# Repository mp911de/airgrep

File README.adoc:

++++
<h1>
<picture>
<source media="(prefers-color-scheme: dark)" srcset="assets/logo-dark@2x.png">

</picture>
</h1>
++++

A portable ADS-B / FLARM receiver based on https://github.com/PantsForBirds/adsbee[ADSBee].
Started as carrier board for a removable ESP32-S3 touch display and https://pantsforbirds.com/product/adsbee-1090u/[ADSBee 1090U] receiver, with a soldered MAX-M10S GNSS receiver.
It adds a single-cell Li-ion charger, a 5 V boost rail, a fuel gauge, a barometer and a buzzer.

.airgrep Screenshot
image::assets/home-screen.png[airgrep Home Screen,30%]

.Traffic Advisory
image::assets/home-ta.png[airgrep Traffic Advisory,30%]

== Features

* 800x480 Capacitive Touchscreen with ESP32 S3 microcontroller (240 MHz, 16 MB Flash, 8 MB PSRAM)
* https://github.com/PantsForBirds/adsbee[ADSBee 1090U] ADS-B receiver with FLARM firmware and GDL90 Broadcast of FLARM traffic (for e.g. Skydemon, Foreflight, …) via WiFi
* https://www.u-blox.com/en/product/max-m10-series[GPS Module], https://www.bosch-sensortec.com/en/products/environmental-sensors/pressure-sensors/bmp580[Pressure Sensor (for barometric Altitude)]
* link:https://github.com/mp911de/daidalus[DAIDALUS] Traffic Advisory engine (Detect and AvoID)
* Buzzer, WiFi (via ADSBee), USB-C Charging Port, Rechargeable Li-Ion Battery
* `airgrep.py` and `airgrep Utility` apps for firmware and device management

=== Ideas for the next revision

* IMU (Accelerometer, Gyro) for Foreflight's AHRS
* USB Switch for easier Firmware upgrades
* Remote Light Sensor for Display brightness control
* https://pantsforbirds.com/adsbee/#adsbee-1421[ADSBee m1421] Module (smaller and cheaper)

== Current state

* [x] Rev A board works
* [ ] Firmware: In progress
** [x] Basic charger and component connectivity
** [x] ADSbe Firmware: Adopted (https://github.com/mp911de/adsbee/tree/flarm)
** [ ] Flarm barometric altitude normalization
* [ ] Planning for Rev B

== Pointers

[width="100%",cols="50%,50%",options="header",]
|===
|Path |Content
|docs/ |Specs, design decisions, mechanics, pin maps, I2C limits,
firmware requirements, USB protocol, hand-sourced BOM, open issues

|issues/ |Local issue tracker, one file per issue

|specs/ |Power model inputs behind the tables in `docs/specs.adoc`

|hardware/ |KiCad projects: `carrier-ti-charger` (active, BQ25798, with
schematic PDF and JLCPCB exports), `carrier-max-charger` (frozen
reference), `insulator`, `sim`

|firmware/ |Display firmware and utility app

|datasheets/ |Data sheets of the parts in use
|===

== License

image::assets/oshw.png[Open Source Hardware,10%]

This project (hardware design and software) is licensed under the link:LICENSE.txt[Apache License 2.0] except where noted.

Firmware builds and the device include third-party components under their own licenses, listed on the device under Licenses and in `firmware/utility/remote/notices/`.
These include:

* https://github.com/mp911de/daidalus[DAIDALUS], NASA Open Source Agreement 1.3
* https://github.com/mp911de/adsbee/tree/flarm[ADSBee firmware] GPL-3.0 (running on the ADSBee receiver with link:https://www.flarm.com/en/integration/flarm-famp-public-protocol/[FLARM FAMP])

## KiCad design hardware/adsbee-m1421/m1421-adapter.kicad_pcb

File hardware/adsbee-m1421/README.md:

# ADSBee m1421 Breakout Board

## Pinout

| Front, J4 pin header | Back, J3 Molex 54722-0204 |
| --- | --- |
|  |  |
| Square pad 1 is at lower left. | Pin 1 is at lower right, beside the silkscreen dot. |

Both views face the adapter with the mounting holes at the top.

| Signal | J4 | J3 | Module pin (U1) | Description |
| --- | --- | --- | --- | --- |
| +5V_IN | 2 | 2, 4 | | 5 V input to the onboard 3.3 V regulator. |
| +3V3 | | 12 | 1, 4, 19, 22 | Unswitched 3.3 V output from the onboard regulator. |
| GND | 1 | 1, 3, 15, 17, 19 | 6, 18, 23, 25, 27, 34, 36, MP | Power and signal return. |
| GNSS_RX | 3 | 6 | 13 | GNSS UART receive. |
| GNSS_TX | 4 | 8 | 12 | GNSS UART transmit. |
| GNSS_PPS | 5 | 10 | 14 | Pulse per second from the GNSS receiver. |
| RESET_N | 6 | 5 | 17 | Drive low to reset the module. |
| JTAG_TMSC | 7 | 7 | 8 | cJTAG data and control, JTAG TMS. |
| JTAG_TCKC | 8 | 9 | 9 | Debug clock. |
| JTAG_TDI | 9 | 11 | 11 | JTAG data input. |
| JTAG_TDO | 10 | 13 | 10 | JTAG data output. |
| MODULE_TX | 11 | 14 | 21 | Module output to host RX. |
| MODULE_RX | 12 | 16 | 20 | Module input from host TX. |
| GNSS_3V3 | 13 | 20 | | Switched 3.3 V output. DIO27 low enables Q1. Bridge JP1 for always-on power. |
| SYNC | 14 | 18 | 28 | High requests sleep, or selects the bootloader at reset. |

Signal levels are 3.3 V. Use one driver per signal shared by J4 and J3.

## Firmware updates

The module updates over its UART ROM bootloader on MODULE_RX and MODULE_TX.

1. Drive SYNC high.
2. Pulse RESET_N low and release it while SYNC stays high.
3. Flash over the UART.
4. Return SYNC low and reset to run the application.

The application console runs at 1 Mbaud by default. JTAG is available on both connectors for recovery. The updater or debug probe is external to this board.

## Links

- [ADSBee m1421 hardware documentation](https://github.com/PantsForBirds/adsbee/blob/main/docs/adsbee-1421/m1421.md)
- [ADSBee 1421 firmware README](https://github.com/PantsForBirds/adsbee/blob/main/firmware/adsbee_1421/README.md)
- [Molex SlimStack family data](https://www.molex.com/content/dam/molex/molex-dot-com/en_us/pdf/datasheets/987652-3791.pdf). J3: 54722-0204, the mating plug is 55560-0207.

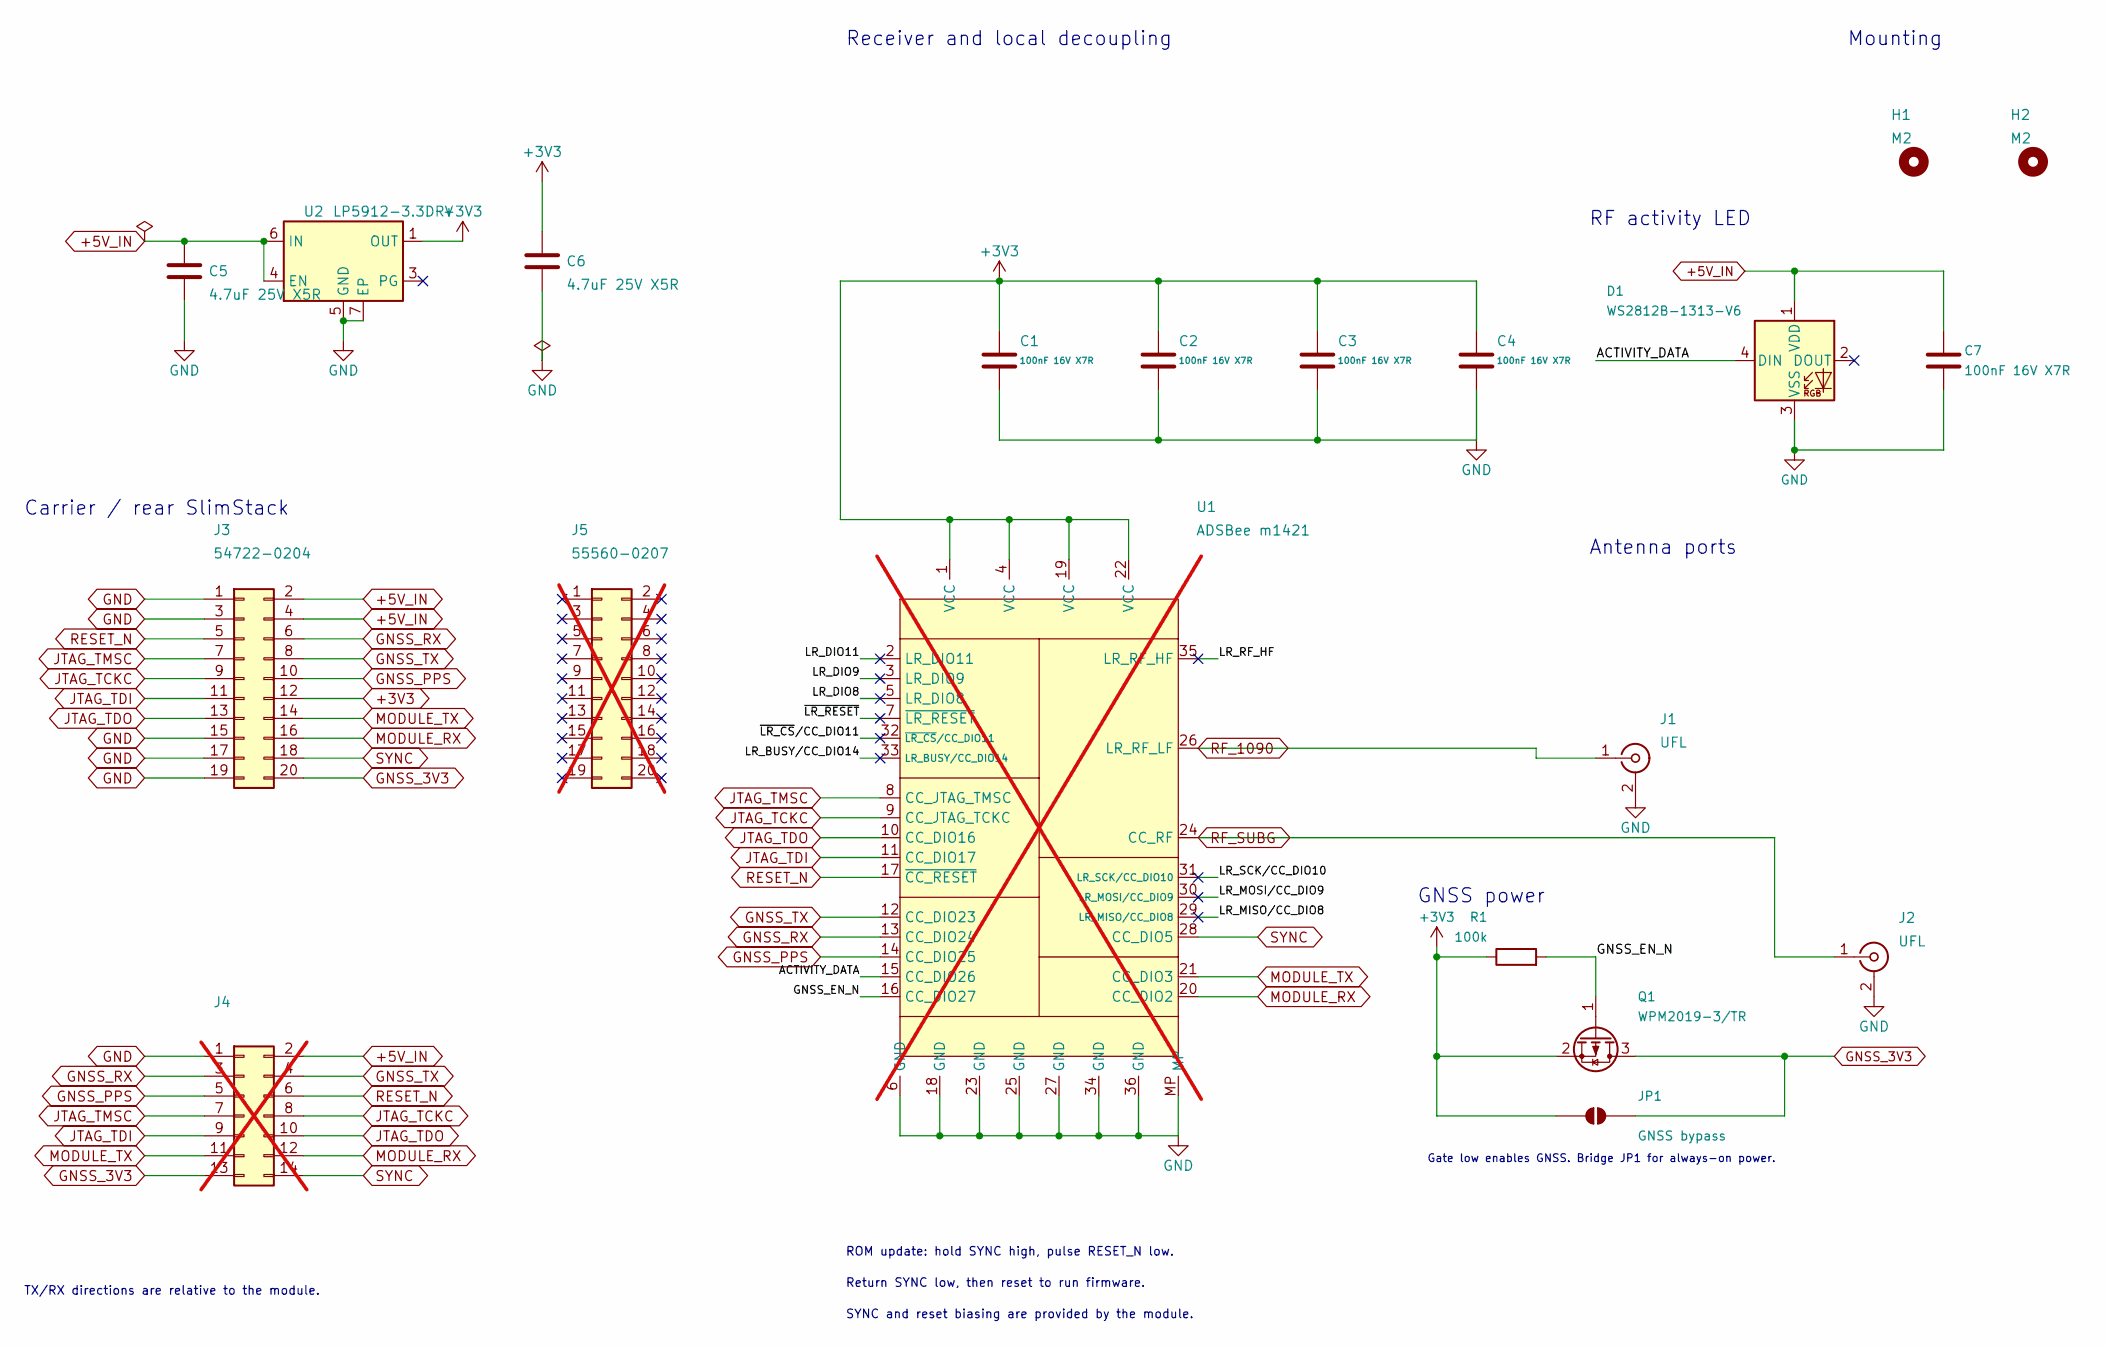
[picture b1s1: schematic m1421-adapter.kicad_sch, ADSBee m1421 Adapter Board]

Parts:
C1, C2, C3, C4, C7: 100nF 16V X7R; C_0402_1005Metric; MPN CL05B104KO5NNNC; LCSC C1525
C5, C6: 4.7uF 25V X5R; C_0805_2012Metric; MPN CL21A475KAQNNNE; LCSC C1779
D1: WS2812B-1313-V6; Worldsemi_WS2812B-1313-V6; MPN WS2812B-1313-V6; LCSC C52941388
H1, H2: M2; MountingHole_2.7mm_M2.5_DIN965
J1, J2: UFL; U.FL_Hirose_U.FL-R-SMT-1_Vertical; MPN U.FL-R-SMT-1(80); LCSC C88374
J3: 54722-0204; Molex_SlimStack_54722-0204_2x10_P0.50mm_Vertical; MPN 547220204; LCSC C588336
J4: PinHeader_2x07_P2.54mm_Vertical; not fitted
J5: 55560-0207; MPN 555600207; LCSC C127345; not fitted
JP1: GNSS bypass; SolderJumper-2_P1.3mm_Open_RoundedPad1.0x1.5mm
Q1: WPM2019-3/TR; SOT-523; MPN WPM2019-3/TR; LCSC C239546
R1: 100k; R_0402_1005Metric; MPN 0402WGF1003TCE; LCSC C25741
U1: ADSBee m1421; PantsForBirds_ADSBee_m1421_Module; not fitted
U2: LP5912-3.3DRV; WSON-6-1EP_2x2mm_P0.65mm_EP1x1.6mm_ThermalVias; MPN LP5912-3.3DRVR; LCSC C524780

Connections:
+3V3: C1.1, C2.1, C3.1, C4.1, C6.1, J3.12, JP1.1 (A), Q1.2 (S), R1.1, U1.1 (VCC), U1.4 (VCC), U1.19 (VCC), U1.22 (VCC), U2.1 (OUT)
+5V_IN: C5.1, C7.1, D1.1 (VDD), J3.2, J3.4, J4.2, U2.4 (EN), U2.6 (IN)
/ACTIVITY_DATA: D1.4 (DIN), U1.15 (CC_DIO26)
/GNSS_EN_N: Q1.1 (G), R1.2, U1.16 (CC_DIO27)
/LR_BUSY/CC_DIO14: U1.33 (LR_BUSY/CC_DIO14)
/LR_DIO8: U1.5 (LR_DIO8)
/LR_DIO9: U1.3 (LR_DIO9)
/LR_DIO11: U1.2 (LR_DIO11)
/LR_MISO/CC_DIO8: U1.29 (LR_MISO/CC_DIO8)
/LR_MOSI/CC_DIO9: U1.30 (LR_MOSI/CC_DIO9)
/LR_RF_HF: U1.35 (LR_RF_HF)
/LR_SCK/CC_DIO10: U1.31 (LR_SCK/CC_DIO10)
/~LR_CS/CC_DIO11: U1.32 (~LR_CS/CC_DIO11)
/~LR_RESET: U1.7 (~LR_RESET)
GND: C1.2, C2.2, C3.2, C4.2, C5.2, C6.2, C7.2, D1.3 (VSS), J1.2 (Ext), J2.2 (Ext), J3.1, J3.3, J3.15, J3.17, J3.19, J4.1, U1.6 (GND), U1.18 (GND), U1.23 (GND), U1.25 (GND), U1.27 (GND), U1.34 (GND), U1.36 (GND), U1.MP, U2.5 (GND), U2.7 (EP)
GNSS_3V3: J3.20, J4.13, JP1.2 (B), Q1.3 (D)
GNSS_PPS: J3.10, J4.5, U1.14 (CC_DIO25)
GNSS_RX: J3.6, J4.3, U1.13 (CC_DIO24)
GNSS_TX: J3.8, J4.4, U1.12 (CC_DIO23)
JTAG_TCKC: J3.9, J4.8, U1.9 (CC_JTAG_TCKC)
JTAG_TDI: J3.11, J4.9, U1.11 (CC_DIO17)
JTAG_TDO: J3.13, J4.10, U1.10 (CC_DIO16)
JTAG_TMSC: J3.7, J4.7, U1.8 (CC_JTAG_TMSC)
MODULE_RX: J3.16, J4.12, U1.20 (CC_DIO2)
MODULE_TX: J3.14, J4.11, U1.21 (CC_DIO3)
RESET_N: J3.5, J4.6, U1.17 (~CC_RESET)
RF_1090: J1.1 (In), U1.26 (LR_RF_LF)
RF_SUBG: J2.1 (In), U1.24 (CC_RF)
SYNC: J3.18, J4.14, U1.28 (CC_DIO5)

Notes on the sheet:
ROM update: hold SYNC high, pulse RESET_N low.
Carrier / rear SlimStack
RF activity LED
Antenna ports
Receiver and local decoupling
GNSS power
Mounting
TX/RX directions are relative to the module.
Gate low enables GNSS. Bridge JP1 for always-on power.
Return SYNC low, then reset to run firmware.
SYNC and reset biasing are provided by the module.

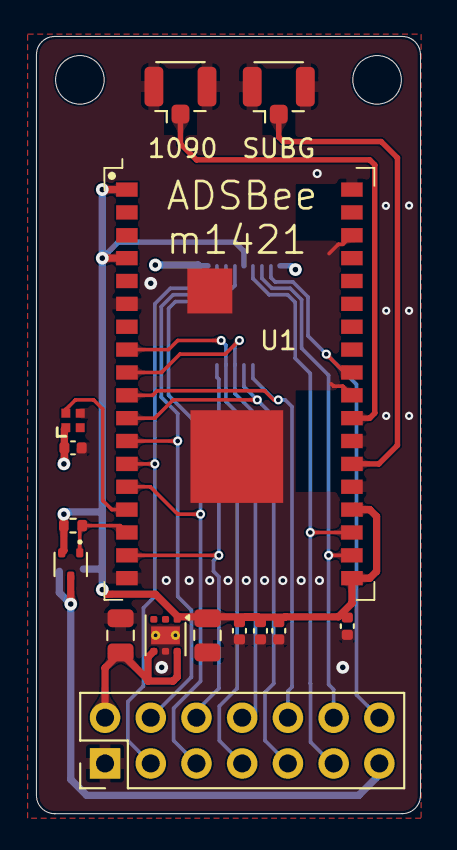
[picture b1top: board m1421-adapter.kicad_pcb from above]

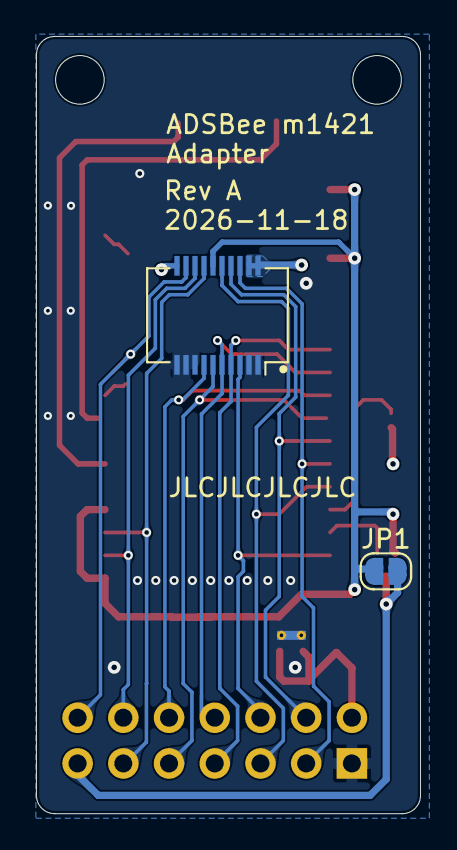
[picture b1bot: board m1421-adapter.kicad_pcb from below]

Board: 4 copper layers, 21.3 x 43.2 mm, 19 parts (2 on the bottom side), 19 nets.

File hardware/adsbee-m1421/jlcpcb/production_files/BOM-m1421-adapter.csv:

Comment,Designator,Footprint,LCSC,Quantity
100k,R1,R_0402_1005Metric,C25741,1
100nF 16V X7R,"C1,C2,C3,C4,C7",C_0402_1005Metric,C1525,5
4.7uF 25V X5R,"C5,C6",C_0805_2012Metric,C1779,2
54722-0204,J3,Molex_SlimStack_54722-0204_2x10_P0.50mm_Vertical,C588336,1
LP5912-3.3DRV,U2,WSON-6-1EP_2x2mm_P0.65mm_EP1x1.6mm_ThermalVias,C524780,1
UFL,"J1,J2",U.FL_Hirose_U.FL-R-SMT-1_Vertical,C88374,2
WPM2019-3/TR,Q1,SOT-523,C239546,1
WS2812B-1313-V6,D1,Worldsemi_WS2812B-1313-V6,C52941388,1

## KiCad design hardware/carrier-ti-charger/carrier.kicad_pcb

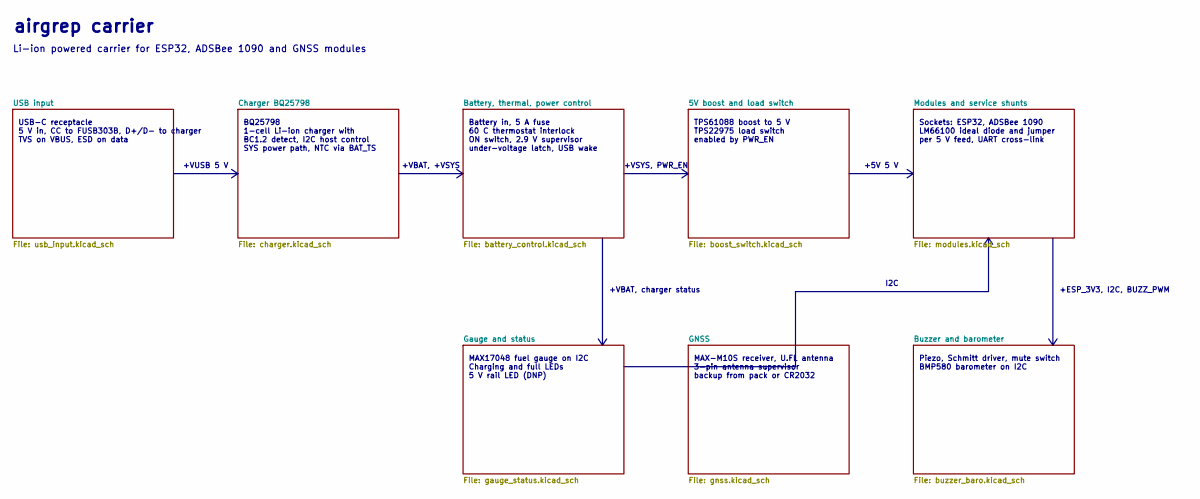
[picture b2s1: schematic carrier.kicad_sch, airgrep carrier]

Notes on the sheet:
I2C
TPS61088 boost to 5 V TPS22975 load switch enabled by PWR_EN
Piezo, Schmitt driver, mute switch BMP580 barometer on I2C
BQ25798 1-cell Li-ion charger with BC1.2 detect, I2C host control SYS power path, NTC via BAT_TS
airgrep carrier
+VBAT, +VSYS
+ESP_3V3, I2C, BUZZ_PWM
+VBAT, charger status
Sockets: ESP32, ADSBee 1090 LM66100 ideal diode and jumper per 5 V feed, UART cross-link
Battery in, 5 A fuse 60 C thermostat interlock ON switch, 2.9 V supervisor under-voltage latch, USB wake
MAX-M10S receiver, U.FL antenna 3-pin antenna supervisor backup from pack or CR2032
+VUSB 5 V
+5V 5 V
USB-C receptacle 5 V in, CC to FUSB303B, D+/D- to charger TVS on VBUS, ESD on data
MAX17048 fuel gauge on I2C Charging and full LEDs 5 V rail LED (DNP)
+VSYS, PWR_EN
Li-ion powered carrier for ESP32, ADSBee 1090 and GNSS modules

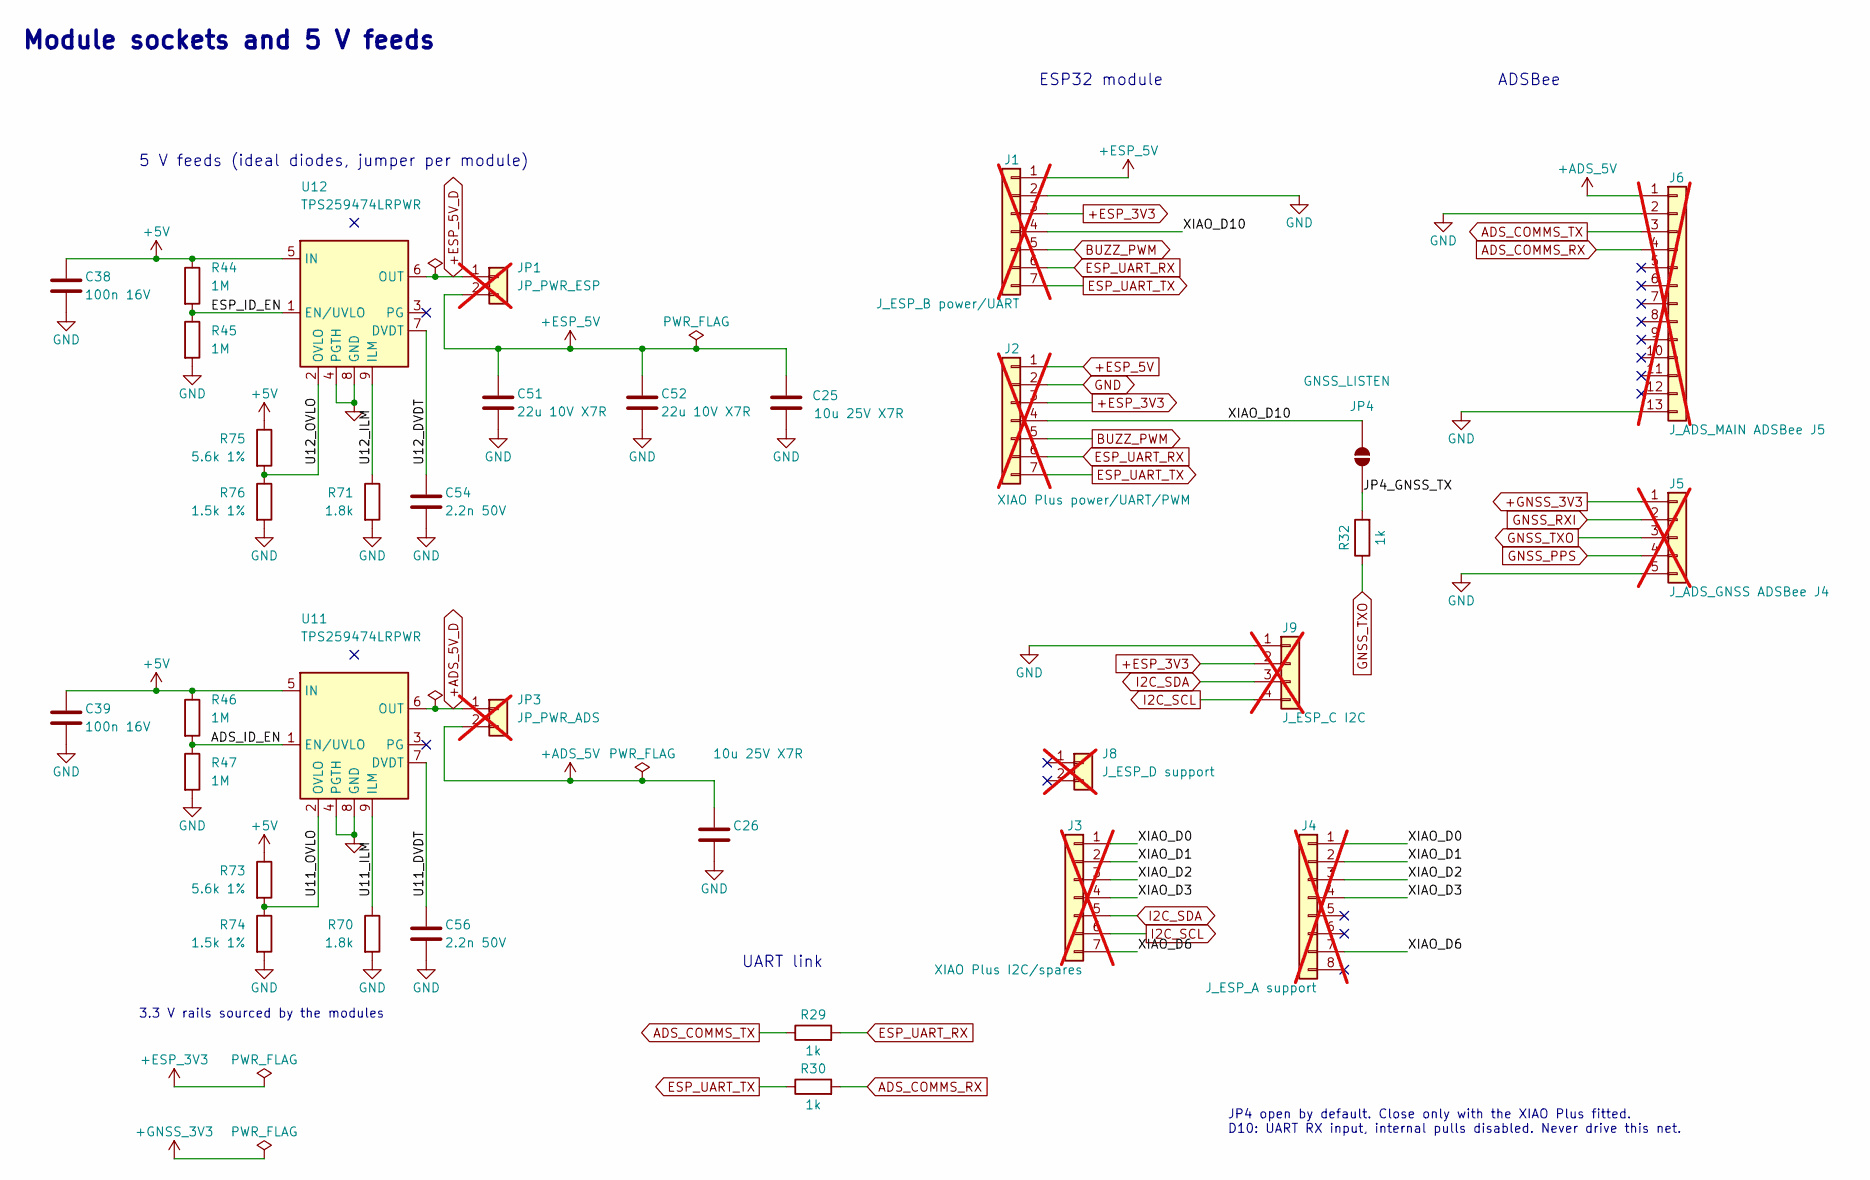
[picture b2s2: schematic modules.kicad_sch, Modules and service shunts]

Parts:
C25, C26: 10u 25V X7R; C_0805_2012Metric; LCSC C3039694
C38, C39: 100n 16V; C_0402_1005Metric_NoSilk; MPN CL05B104KO5NNNC; LCSC C1525
C51, C52: 22u 10V X7R; C_0805_2012Metric; LCSC C907991
C54, C56: 2.2n 50V; C_0603_1608Metric; MPN 0603B222K500NT; LCSC C1604
J1: J_ESP_B power/UART; PinSocket_1x07_P2.54mm_Vertical; not fitted
J2: XIAO Plus power/UART/PWM; PinHeader_1x07_P2.54mm_Vertical; not fitted
J3: XIAO Plus I2C/spares; PinHeader_1x07_P2.54mm_Vertical; not fitted
J4: J_ESP_A support; PinSocket_1x08_P2.54mm_Vertical; not fitted
J5: J_ADS_GNSS ADSBee J4; PinSocket_1x05_P2.54mm_Vertical; not fitted
J6: J_ADS_MAIN ADSBee J5; PinSocket_1x13_P2.54mm_Vertical; not fitted
J8: J_ESP_D support; PinSocket_1x02_P2.54mm_Vertical; not fitted
J9: J_ESP_C I2C; PinSocket_1x04_P2.54mm_Vertical; not fitted
JP1: JP_PWR_ESP; PinHeader_1x02_P2.54mm_Vertical; not fitted
JP3: JP_PWR_ADS; PinHeader_1x02_P2.54mm_Vertical; not fitted
JP4: GNSS_LISTEN; SolderJumper-2_P1.3mm_Open_RoundedPad1.0x1.5mm
R29, R30, R32: 1k; R_0603_1608Metric; LCSC C21190
R44, R45, R46, R47: 1M; R_0603_1608Metric; LCSC C22935
R70, R71: 1.8k; R_0603_1608Metric; Tolerance 1%; MPN 0603WAF1801T5E; LCSC C4177
R73, R75: 5.6k 1%; R_0603_1608Metric; Tolerance 1%; MPN 0603WAF5601T5E; LCSC C23189
R74, R76: 1.5k 1%; R_0402_1005Metric_NoSilk; Tolerance 1%; MPN 0402WGF1501TCE; LCSC C25867
U11, U12: TPS259474LRPWR; VQFN-10_L2.0-W2.0-P0.45-HR_LM73100; LCSC C2864845

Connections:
+5V: C38.1, C39.1, R44.1, R46.1, R73.1, R75.1, U11.5 (IN), U12.5 (IN); also elsewhere on the board
+ADS_5V: C26.1, J6.1, JP3.2
+ADS_5V_D: JP3.1, U11.6 (OUT)
+ESP_3V3: J1.3, J2.3, J9.2; also elsewhere on the board
+ESP_5V: C25.1, C51.1, C52.1, J1.1, J2.1, JP1.2
+ESP_5V_D: JP1.1, U12.6 (OUT); also elsewhere on the board
+GNSS_3V3: J5.1; also elsewhere on the board
/Modules and service shunts/ADS_ID_EN: R46.2, R47.1, U11.1 (EN/UVLO)
/Modules and service shunts/ESP_ID_EN: R44.2, R45.1, U12.1 (EN/UVLO)
/Modules and service shunts/JP4_GNSS_TX: JP4.1 (A), R32.2
/Modules and service shunts/U11_DVDT: C56.1, U11.7 (DVDT)
/Modules and service shunts/U11_ILM: R70.1, U11.9 (ILM)
/Modules and service shunts/U11_OVLO: R73.2, R74.1, U11.2 (OVLO)
/Modules and service shunts/U12_DVDT: C54.1, U12.7 (DVDT)
/Modules and service shunts/U12_ILM: R71.1, U12.9 (ILM)
/Modules and service shunts/U12_OVLO: R75.2, R76.1, U12.2 (OVLO)
/Modules and service shunts/XIAO_D0: J3.1, J4.1
/Modules and service shunts/XIAO_D1: J3.2, J4.2
/Modules and service shunts/XIAO_D2: J3.3, J4.3
/Modules and service shunts/XIAO_D3: J3.4, J4.4
/Modules and service shunts/XIAO_D6: J3.7, J4.7
/Modules and service shunts/XIAO_D10: J1.4, J2.4, JP4.2 (B)
ADS_COMMS_RX: J6.4, R30.2
ADS_COMMS_TX: J6.3, R29.1
BUZZ_PWM: J1.5, J2.5; also elsewhere on the board
ESP_UART_RX: J1.6, J2.6, R29.2
ESP_UART_TX: J1.7, J2.7, R30.1
GND: C25.2, C26.2, C38.2, C39.2, C51.2, C52.2, C54.2, C56.2, J1.2, J2.2, J5.5, J6.2, J6.13, J9.1, R45.2, R47.2, R70.2, R71.2, R74.2, R76.2, U11.4 (PGTH), U11.8 (GND), U12.4 (PGTH), U12.8 (GND); also elsewhere on the board
GNSS_PPS: J5.4; also elsewhere on the board
GNSS_RXI: J5.2; also elsewhere on the board
GNSS_TXO: J5.3, R32.1; also elsewhere on the board
I2C_SCL: J3.6, J9.4; also elsewhere on the board
I2C_SDA: J3.5, J9.3; also elsewhere on the board

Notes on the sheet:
Module sockets and 5 V feeds
UART link
ADSBee
3.3 V rails sourced by the modules
JP4 open by default. Close only with the XIAO Plus fitted. D10: UART RX input, internal pulls disabled. Never drive this net.
5 V feeds (ideal diodes, jumper per module)
ESP32 module

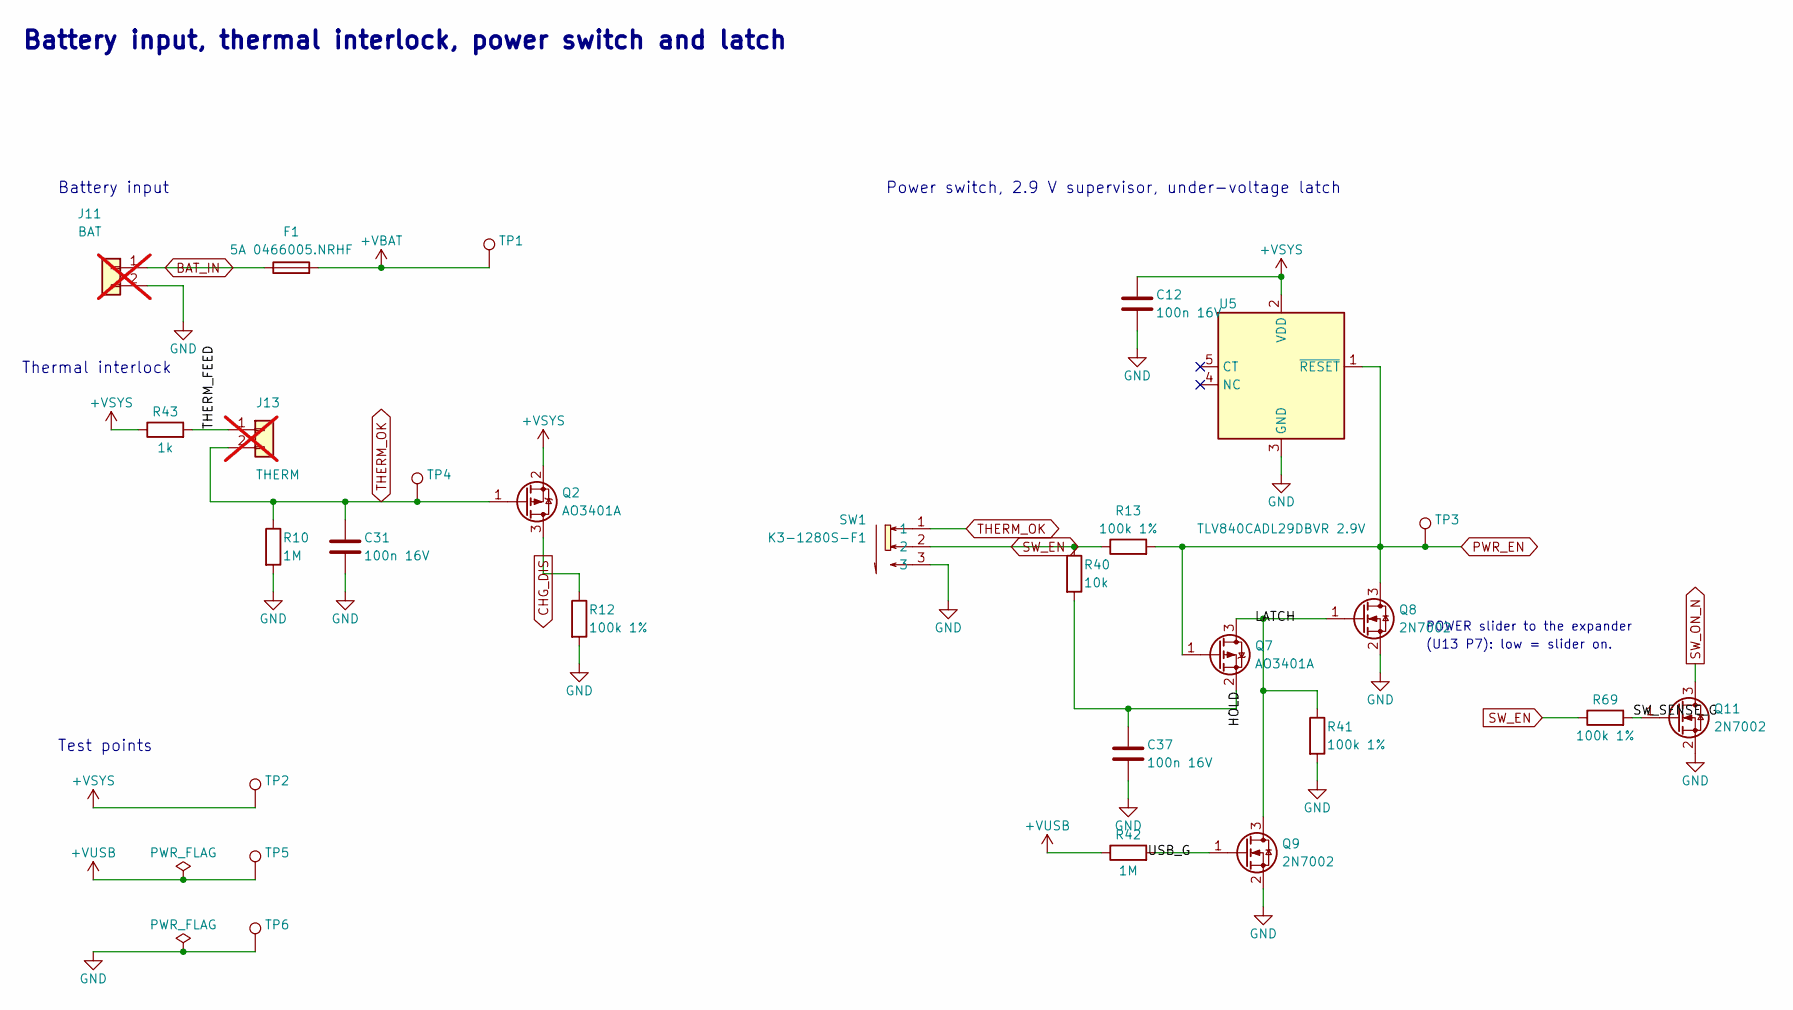
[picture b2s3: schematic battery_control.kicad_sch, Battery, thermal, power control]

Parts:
C12, C31, C37: 100n 16V; C_0402_1005Metric_NoSilk; MPN CL05B104KO5NNNC; LCSC C1525
F1: 5A 0466005.NRHF; Fuse_1206_3216Metric; LCSC C57525
J11: BAT; JST_PH_B2B-PH-K_1x02_P2.00mm_Vertical_R10; not fitted
J13: THERM; JST_PH_B2B-PH-K_1x02_P2.00mm_Vertical_R10; not fitted
Q2, Q7: AO3401A; SOT-23; LCSC C15127
Q8, Q9, Q11: 2N7002; SOT-23; LCSC C8545
R10, R42: 1M; R_0603_1608Metric; LCSC C22935
R12, R13, R41, R69: 100k 1%; R_0603_1608Metric; LCSC C25803
R40: 10k; R_0603_1608Metric; LCSC C25804
R43: 1k; R_0603_1608Metric; LCSC C21190
SW1: K3-1280S-F1; SW-SMD_K3-1280S-F1; LCSC C92658
TP1: +VBAT; TestPoint_Pad_D1.5mm
TP2: +VSYS; TestPoint_Pad_D1.5mm
TP3: PWR_EN; TestPoint_Pad_D1.5mm
TP4: THERM_OK; TestPoint_Pad_D1.5mm
TP5: +VUSB; TestPoint_Pad_D1.5mm
TP6: GND; TestPoint_Pad_D1.5mm
U5: TLV840CADL29DBVR 2.9V; SOT-23-5_L2.9-W1.6-P0.95-LS2.8-BR; LCSC C3686404

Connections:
+VBAT: F1.2, TP1.1 (1_1); also elsewhere on the board
+VSYS: C12.1, Q2.2 (S), R43.1, TP2.1 (1_1), U5.2 (VDD); also elsewhere on the board
+VUSB: R42.1, TP5.1 (1_1); also elsewhere on the board
/Battery, thermal, power control/HOLD: C37.2, Q7.2 (S), R40.2
/Battery, thermal, power control/LATCH: Q7.3 (D), Q8.1 (G), Q9.3 (D), R41.1
/Battery, thermal, power control/SW_SENSE_G: Q11.1 (G), R69.2
/Battery, thermal, power control/THERM_FEED: J13.1, R43.2
/Battery, thermal, power control/USB_G: Q9.1 (G), R42.2
BAT_IN: F1.1, J11.1
CHG_DIS: Q2.3 (D), R12.1; also elsewhere on the board
GND: C12.2, C31.2, C37.1, J11.2, Q8.2 (S), Q9.2 (S), Q11.2 (S), R10.2, R12.2, R41.2, SW1.3, TP6.1 (1_1), U5.3 (GND); also elsewhere on the board
PWR_EN: Q7.1 (G), Q8.3 (D), R13.2, TP3.1 (1_1), U5.1 (~RESET); also elsewhere on the board
SW_EN: R13.1, R40.1, R69.1, SW1.2; also elsewhere on the board
SW_ON_N: Q11.3 (D); also elsewhere on the board
THERM_OK: C31.1, J13.2, Q2.1 (G), R10.1, SW1.1, TP4.1 (1_1)

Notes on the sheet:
Battery input
Battery input, thermal interlock, power switch and latch
Power switch, 2.9 V supervisor, under-voltage latch
Test points
(U13 P7): low = slider on.
Thermal interlock
POWER slider to the expander

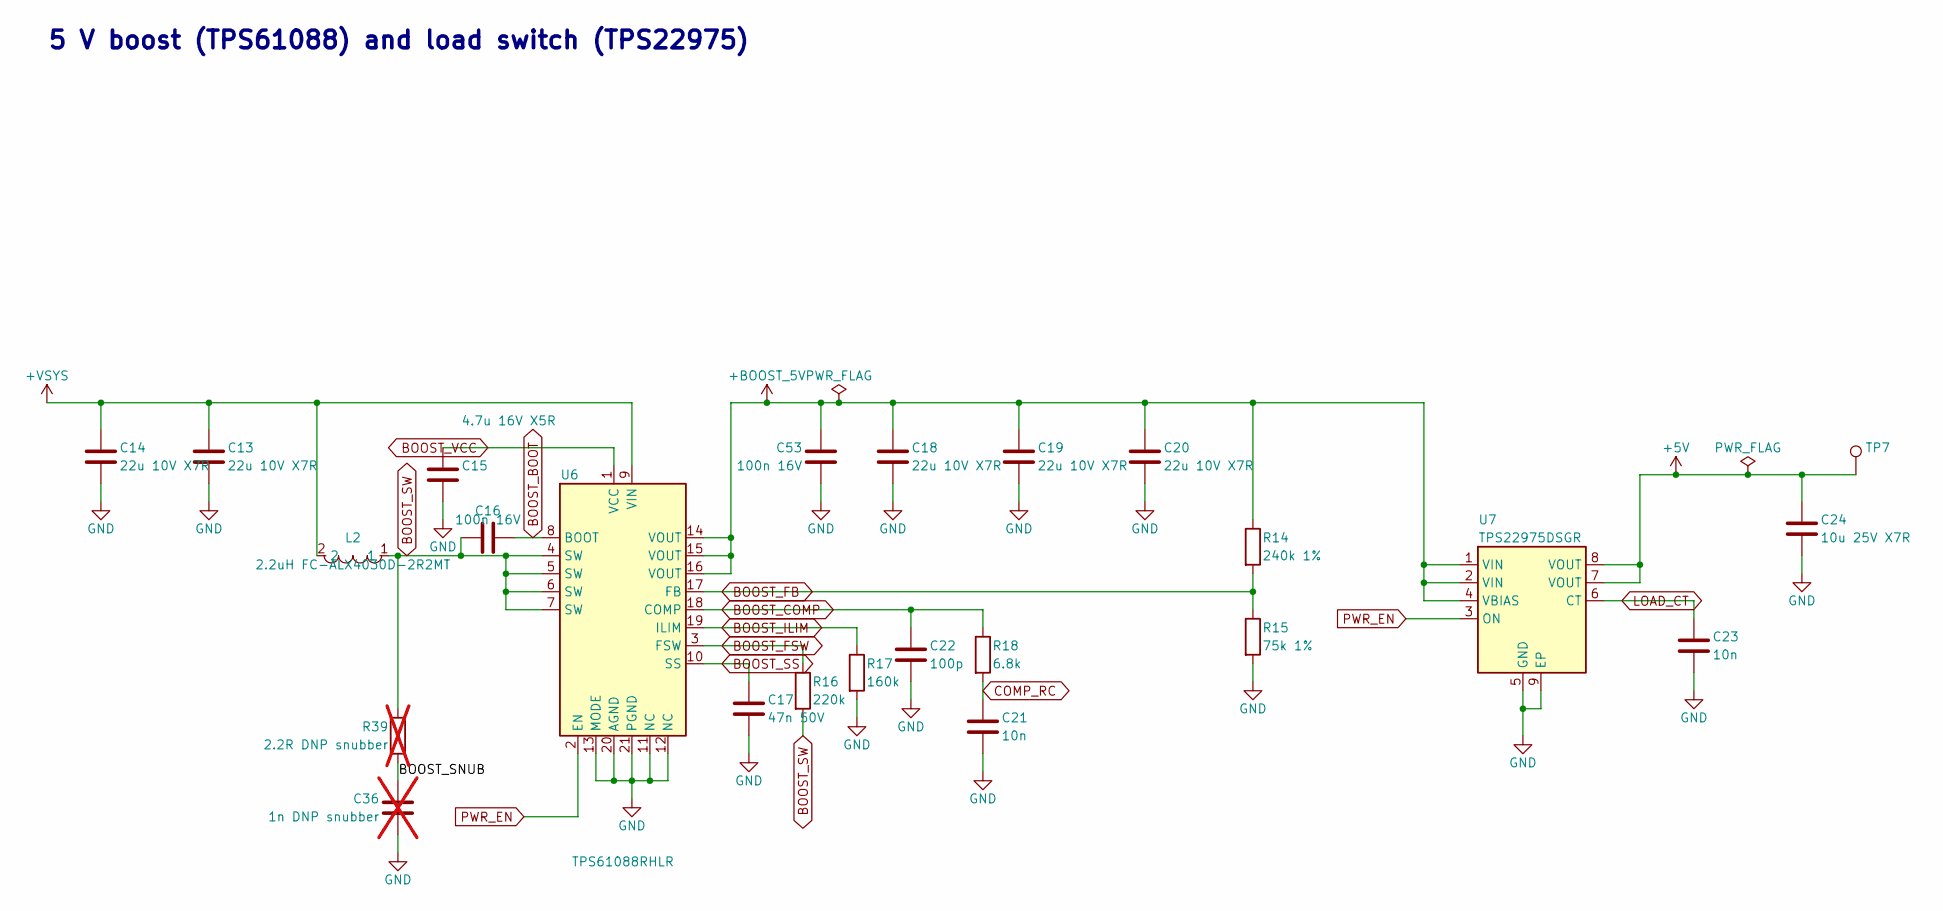
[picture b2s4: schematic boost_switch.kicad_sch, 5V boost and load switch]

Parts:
C13, C14, C18, C19, C20: 22u 10V X7R; C_0805_2012Metric; LCSC C907991
C15: 4.7u 16V X5R; C_0603_1608Metric; LCSC C19666
C16, C53: 100n 16V; C_0402_1005Metric_NoSilk; MPN CL05B104KO5NNNC; LCSC C1525
C17: 47n 50V; C_0603_1608Metric; LCSC C1622
C21, C23: 10n; C_0603_1608Metric; LCSC C57112
C22: 100p; C_0603_1608Metric; LCSC C14858
C24: 10u 25V X7R; C_0805_2012Metric; LCSC C3039694
C36: 1n DNP snubber; C_0603_1608Metric; not fitted
L2: 2.2uH FC-ALX4030D-2R2MT; IND-SMD_L4.2-W4.2_FC-ALX4030D; LCSC C5370906
R14: 240k 1%; R_0603_1608Metric; LCSC C4197
R15: 75k 1%; R_0603_1608Metric; LCSC C23242
R16: 220k; R_0603_1608Metric; LCSC C22961
R17: 160k; R_0603_1608Metric; LCSC C22813
R18: 6.8k; R_0603_1608Metric; LCSC C23212
R39: 2.2R DNP snubber; R_0603_1608Metric; not fitted
TP7: +5V; TestPoint_Pad_D1.5mm
U6: TPS61088RHLR; VQFN-20_L4.6-W3.6-P0.50-BL; LCSC C87357
U7: TPS22975DSGR; Texas_DSG0008A_WSON-8-1EP_2x2mm_P0.5mm_EP0.9x1.6mm; LCSC C524777

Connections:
+5V: C24.1, TP7.1 (1_1), U7.7 (VOUT), U7.8 (VOUT); also elsewhere on the board
+BOOST_5V: C18.1, C19.1, C20.1, C53.1, R14.1, U6.14 (VOUT), U6.15 (VOUT), U6.16 (VOUT), U7.1 (VIN), U7.2 (VIN), U7.4 (VBIAS)
+VSYS: C13.1, C14.1, L2.2, U6.9 (VIN); also elsewhere on the board
/5V boost and load switch/BOOST_SNUB: C36.1, R39.2
BOOST_BOOT: C16.1, U6.8 (BOOT)
BOOST_COMP: C22.1, R18.1, U6.18 (COMP)
BOOST_FB: R14.2, R15.1, U6.17 (FB)
BOOST_FSW: R16.1, U6.3 (FSW)
BOOST_ILIM: R17.1, U6.19 (ILIM)
BOOST_SS: C17.1, U6.10 (SS)
BOOST_SW: C16.2, L2.1, R16.2, R39.1, U6.4 (SW), U6.5 (SW), U6.6 (SW), U6.7 (SW)
BOOST_VCC: C15.1, U6.1 (VCC)
COMP_RC: C21.1, R18.2
GND: C13.2, C14.2, C15.2, C17.2, C18.2, C19.2, C20.2, C21.2, C22.2, C23.2, C24.2, C36.2, C53.2, R15.2, R17.2, U6.11 (NC), U6.12 (NC), U6.13 (MODE), U6.20 (AGND), U6.21 (PGND), U7.5 (GND), U7.9 (EP); also elsewhere on the board
LOAD_CT: C23.1, U7.6 (CT)
PWR_EN: U6.2 (EN), U7.3 (ON); also elsewhere on the board

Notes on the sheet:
5 V boost (TPS61088) and load switch (TPS22975)

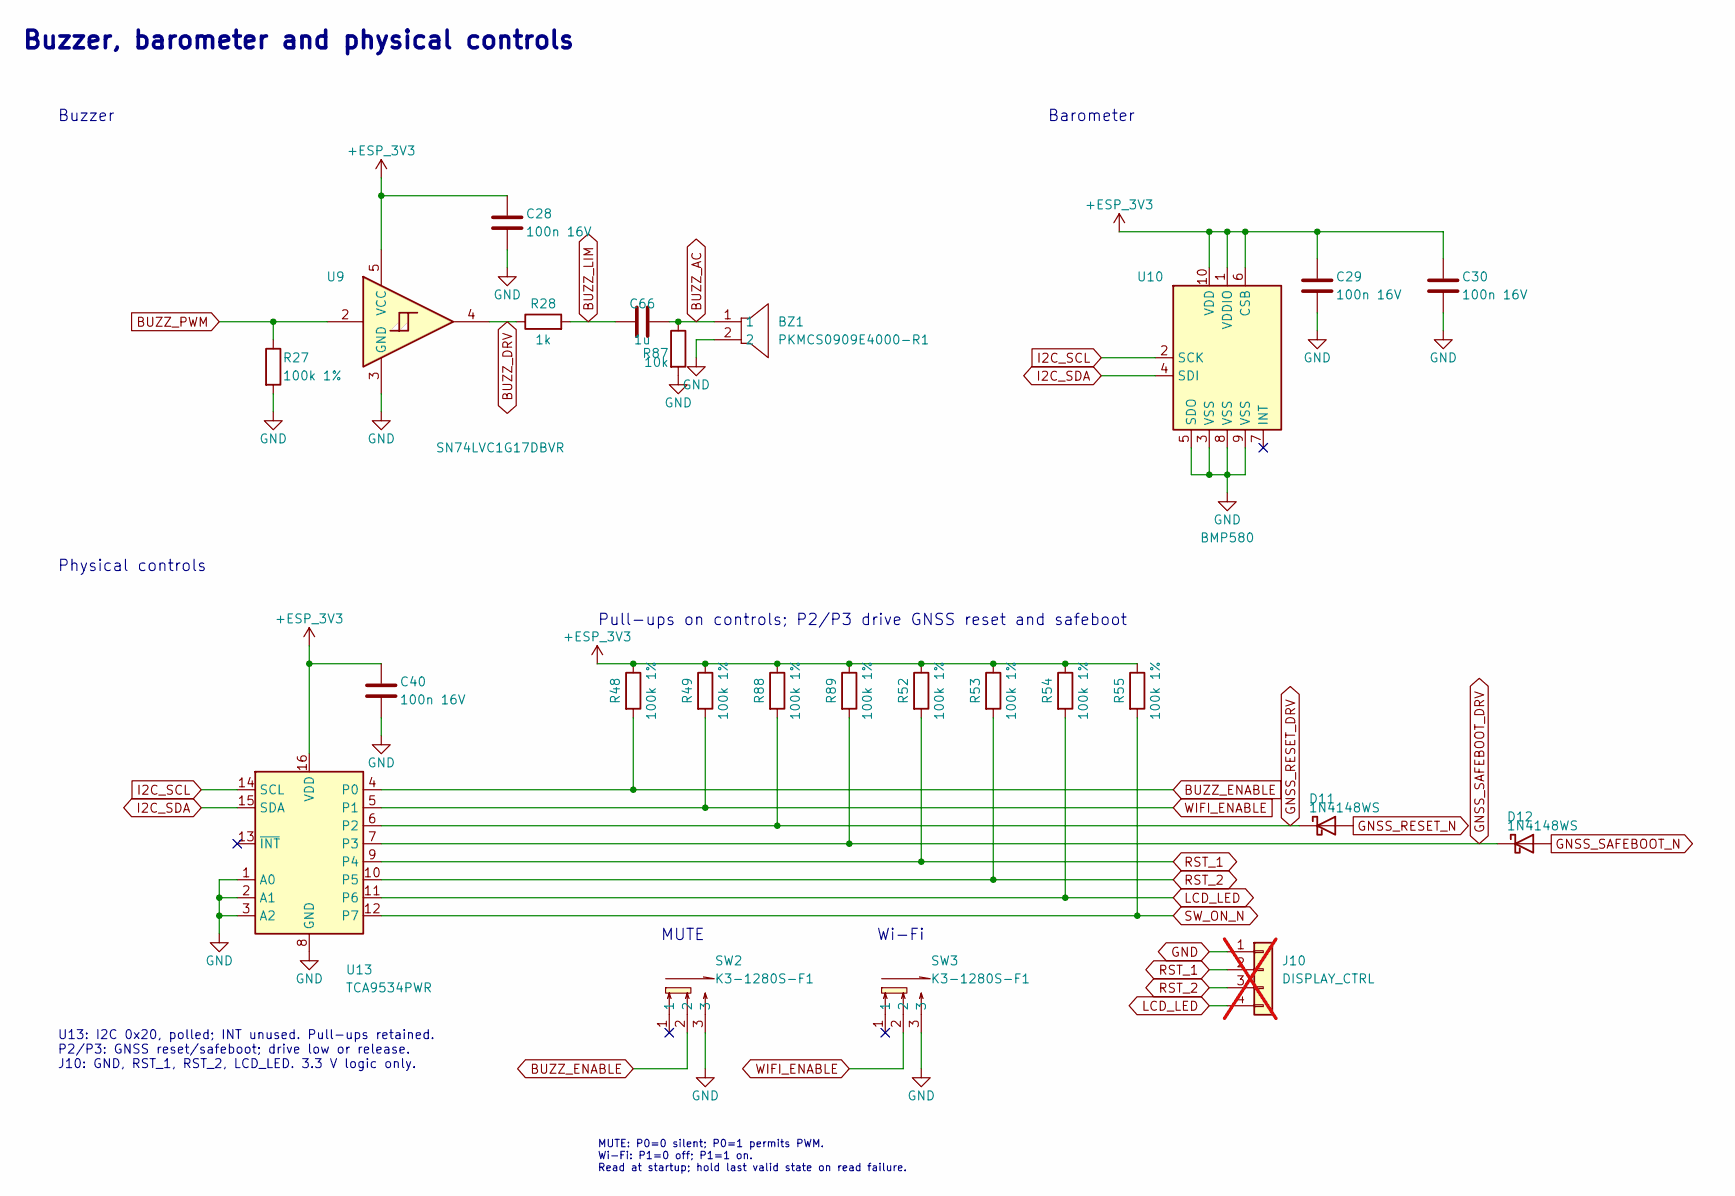
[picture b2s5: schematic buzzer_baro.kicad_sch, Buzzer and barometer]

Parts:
BZ1: PKMCS0909E4000-R1; BUZ-SMD_L9.0-W9.0_PKMCS0909E4000-R1; LCSC C910763
C28, C29, C30, C40: 100n 16V; C_0402_1005Metric_NoSilk; MPN CL05B104KO5NNNC; LCSC C1525
C66: 1u; C_0603_1608Metric; MPN CL10A105KB8NNNC; LCSC C15849
D11, D12: 1N4148WS; D_SOD-323; MPN 1N4148WS; LCSC C2128
J10: DISPLAY_CTRL; PinHeader_1x04_P2.54mm_Vertical; not fitted
R27, R48, R49, R52, R53, R54, R55, R88, R89: 100k 1%; R_0603_1608Metric; LCSC C25803
R28: 1k; R_0603_1608Metric; LCSC C21190
R87: 10k; R_0402_1005Metric_NoSilk; MPN 0402WGF1002TCE; LCSC C25744
SW2, SW3: K3-1280S-F1; SW-SMD_K3-1280S-F1; LCSC C92658
U9: SN74LVC1G17DBVR; SOT-23-5; LCSC C7836
U10: BMP580; LGA-10_L2.0-W2.0-P0.50-TL_BMP581; MPN BMP580; LCSC C22391138
U13: TCA9534PWR; TSSOP-16_4.4x5mm_P0.65mm; LCSC C783615

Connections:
+ESP_3V3: C28.1, C29.1, C30.1, C40.1, R48.1, R49.1, R52.1, R53.1, R54.1, R55.1, R88.1, R89.1, U9.5 (VCC), U10.1 (VDDIO), U10.6 (CSB), U10.10 (VDD), U13.16 (VDD); also elsewhere on the board
BUZZ_AC: BZ1.1, C66.2, R87.1
BUZZ_DRV: R28.1, U9.4
BUZZ_ENABLE: R48.2, SW2.2, U13.4 (P0)
BUZZ_LIM: C66.1, R28.2
BUZZ_PWM: R27.1, U9.2; also elsewhere on the board
GND: BZ1.2, C28.2, C29.2, C30.2, C40.2, J10.1, R27.2, R87.2, SW2.3, SW3.3, U9.3 (GND), U10.3 (VSS), U10.5 (SDO), U10.8 (VSS), U10.9 (VSS), U13.1 (A0), U13.2 (A1), U13.3 (A2), U13.8 (GND); also elsewhere on the board
GNSS_RESET_DRV: D11.1 (K), R88.2, U13.6 (P2)
GNSS_RESET_N: D11.2 (A); also elsewhere on the board
GNSS_SAFEBOOT_DRV: D12.1 (K), R89.2, U13.7 (P3)
GNSS_SAFEBOOT_N: D12.2 (A); also elsewhere on the board
I2C_SCL: U10.2 (SCK), U13.14 (SCL); also elsewhere on the board
I2C_SDA: U10.4 (SDI), U13.15 (SDA); also elsewhere on the board
LCD_LED: J10.4, R54.2, U13.11 (P6)
RST_1: J10.2, R52.2, U13.9 (P4)
RST_2: J10.3, R53.2, U13.10 (P5)
SW_ON_N: R55.2, U13.12 (P7); also elsewhere on the board
WIFI_ENABLE: R49.2, SW3.2, U13.5 (P1)

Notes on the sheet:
Wi-Fi
Barometer
MUTE: P0=0 silent; P0=1 permits PWM. Wi-Fi: P1=0 off; P1=1 on. Read at startup; hold last valid state on read failure.
Buzzer, barometer and physical controls
Physical controls
U13: I2C 0x20, polled; INT unused. Pull-ups retained. P2/P3: GNSS reset/safeboot; drive low or release. J10: GND, RST_1, RST_2, LCD_LED. 3.3 V logic only.
Pull-ups on controls; P2/P3 drive GNSS reset and safeboot
Buzzer
MUTE
